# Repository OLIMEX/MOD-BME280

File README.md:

# MOD-BME280
BME280 precise Humidity, Temperature and Pressure sensor with UEXT and Breadboard connectors

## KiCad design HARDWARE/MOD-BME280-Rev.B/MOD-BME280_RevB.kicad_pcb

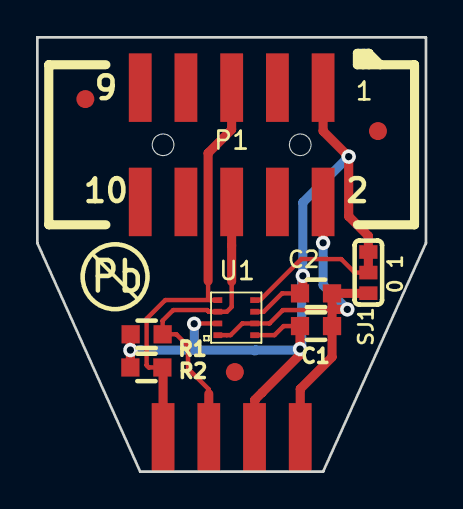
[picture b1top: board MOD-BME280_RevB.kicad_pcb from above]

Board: 2 copper layers, 21.6 x 24.1 mm, 8 parts (0 on the bottom side), 5 nets.

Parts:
C1, C2: 100nF; C_0603_5MIL_DWS
P1: Conn_02x05_Odd_Even; GBH-254-SMT-10_Smaller
P2: Conn_01x04; SIP4_SMD
R1, R2: 4.7K; R_0603_5MIL_DWS
SJ1: SJ2W_Closed(1-2); SJ_2_SMALL_12_TIED
U1: BME280

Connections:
/SCL: P1.5, P2.4, R1.2, U1.4
/SDA: P1.6, P2.3, R2.2, U1.3
GND: C1.2, C2.2, P1.2, P2.1, SJ1.3, U1.1, U1.7
unnamed: C1.1, C2.1, P1.1, P2.2, R1.1, R2.1, SJ1.1, U1.2, U1.6, U1.8
unnamed: SJ1.2, U1.5

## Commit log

2018-03-26 Create LICENSE
2018-03-27 Initial upload of hardware CA files and Arduino demo
2018-03-27 update demo code
2018-04-04 libs fixed
2018-04-04 not needed
2018-04-04 not used
2018-04-04 cache library not used
2021-04-07 Update
    Revision B
2021-08-20 Update
    I2C address changed from 0x76 to 0x77 to match the value defined by the default hardware position of the jumper.
